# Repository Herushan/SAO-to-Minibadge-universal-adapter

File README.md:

# SAO-to-Minibadge-universal-adapter
This is a minibadge format adapter that can be soldered for SAO to Minibadge or Minibadge to SAO usage. This will allow Minibadges to be used on DEFCON badges or SAOs used on Minibadge displays/badges.

All the PCB KiCad files are provided with the gerber zip so you can just buy the boards with that.

Parts are simple with just 16 male header pins or 2 female single row 8 hole adapter and then either a male or female SAO adapter depending on which way you are going. See video below for details. Images of completedd boards and boards back and front.

The video on how to solder and make this adapter is here:
https://youtu.be/1QgKpa0yQGg

Still figuring out the best license for this but for personal use and please do not sell this item.

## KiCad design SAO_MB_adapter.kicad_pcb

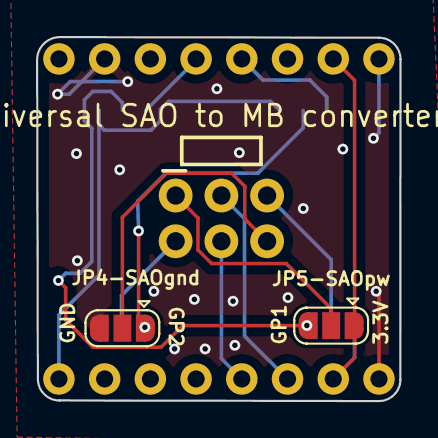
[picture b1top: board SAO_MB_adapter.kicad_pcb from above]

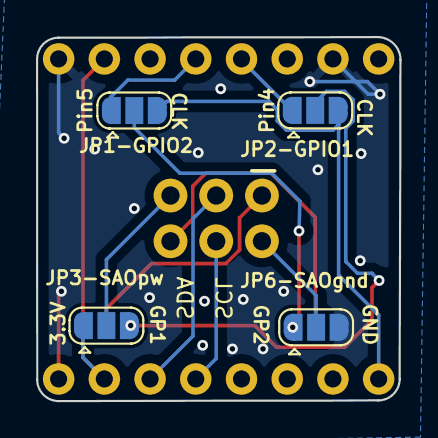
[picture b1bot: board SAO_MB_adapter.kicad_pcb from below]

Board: 2 copper layers, 20.2 x 20.2 mm, 8 parts (4 on the bottom side), 13 nets.

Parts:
J1: CONN_03X2FEMALE; 2X3-SHROUDED
JP1-GPIO2, JP2-GPIO1, JP3-SAOpw, JP4-SAOgnd, JP5-SAOpw, JP6-SAOgnd: SolderJumper_3_Open; SolderJumper-3_P1.3mm_Open_RoundedPad1.0x1.5mm
MB1: MiniBadge_Full

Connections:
+3.3V: JP3-SAOpw.1 (A), JP5-SAOpw.1 (A), MB1.7 (+3V3), MB1.15 (3V3+)
CLK: JP1-GPIO2.3 (B), JP2-GPIO1.3 (B), MB1.9 (CLK)
GND: JP4-SAOgnd.3 (B), JP6-SAOgnd.3 (B), MB1.2 (GND), MB1.8 (GND), MB1.16 (GND)
GPIO1: JP2-GPIO1.2 (C), JP3-SAOpw.3 (B), JP5-SAOpw.3 (B)
GPIO2: JP1-GPIO2.2 (C), JP4-SAOgnd.1 (A), JP6-SAOgnd.1 (A)
Prog/MISO: JP1-GPIO2.1 (A), MB1.5 (PROG3)
Prog/MOSI: JP2-GPIO1.1 (A), MB1.4 (PROG2)
SAO_1: J1.1, JP3-SAOpw.2 (C)
SAO_2: J1.2, JP4-SAOgnd.2 (C)
SAO_3: J1.5, JP5-SAOpw.2 (C)
SAO_4: J1.6, JP6-SAOgnd.2 (C)
SCL: J1.4, MB1.13 (SCL)
SDA: J1.3, MB1.14 (SDA)
